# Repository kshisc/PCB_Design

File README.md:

# Raspberry Pi Sensor ADC Interface PCB
This is a Raspberry Pi–compatible PCB shield designed in KiCad to enable analog sensor interfacing through an MCP3008 SPI-based ADC. The board integrates light and sound sensor input headers along with LED output circuitry. The design process included schematic capture, PCB layout, component selection, and routing of SPI and GPIO connections to ensure reliable communication between the Raspberry Pi and external sensors. After fabrication, the board was assembled using through-hole soldering and validated with a Python test program that reads sensor data via the MCP3008, outputs real-time light and sound values, and drives LED feedback based on configurable thresholds.

(front)

(back)

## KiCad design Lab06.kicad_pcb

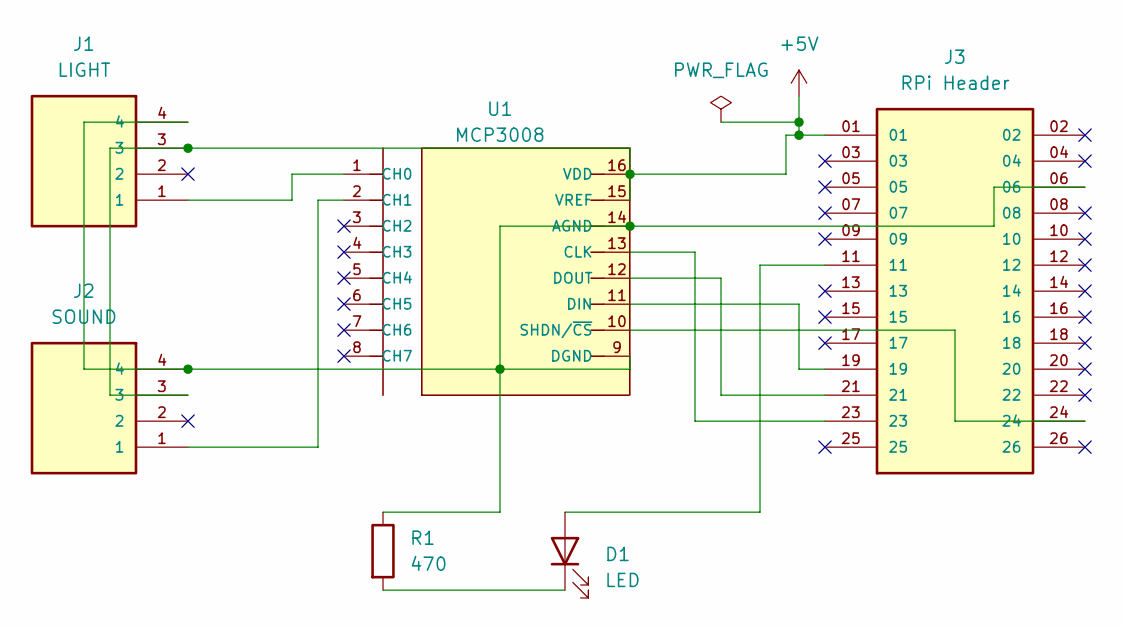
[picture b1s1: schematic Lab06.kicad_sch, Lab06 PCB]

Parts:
D1: LED; LED_D5.0mm
J1: LIGHT; Grover_Connector; PARTREV A
J2: SOUND; Grover_Connector; PARTREV A
J3: RPi Header; RPi_Header; PARTREV R
R1: 470; R_Axial_DIN0204_L3.6mm_D1.6mm_P5.08mm_Horizontal
U1: MCP3008; DIP16-2.54-19.2X7.62MM; MPN MCP3008-I/P

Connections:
+5V: J1.3, J2.3, J3.01, U1.15 (VREF), U1.16 (VDD)
unnamed: D1.2 (A), J3.11
unnamed: D1.1 (K), R1.2
unnamed: J1.4, J2.4, J3.06, R1.1, U1.9 (DGND), U1.14 (AGND)
unnamed: J1.1, U1.1 (CH0)
unnamed: J2.1, U1.2 (CH1)
unnamed: J3.23, U1.13 (CLK)
unnamed: J3.19, U1.11 (DIN)
unnamed: J3.21, U1.12 (DOUT)
unnamed: J3.24, U1.10 (SHDN/~CS)

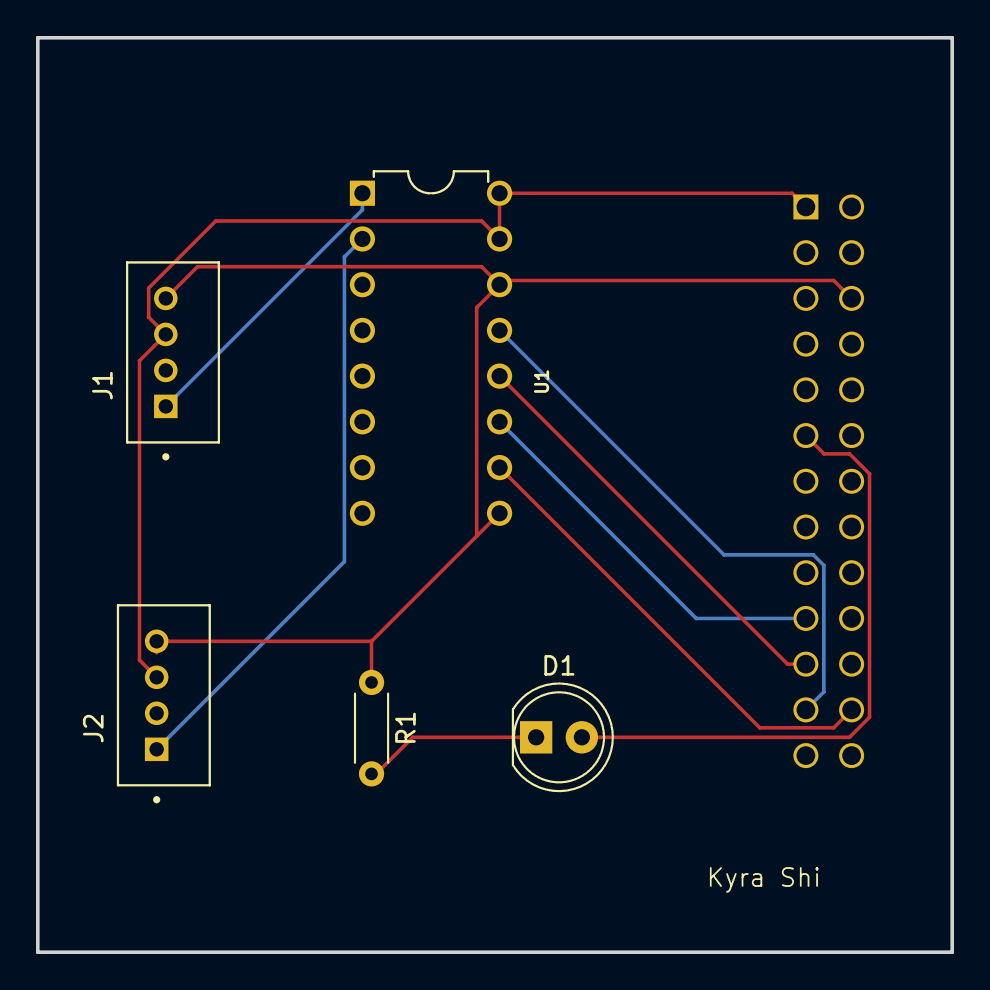
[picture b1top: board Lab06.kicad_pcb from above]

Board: 2 copper layers, 50.8 x 50.8 mm, 6 parts (1 on the bottom side), 10 nets.

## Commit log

2026-04-21 complete
